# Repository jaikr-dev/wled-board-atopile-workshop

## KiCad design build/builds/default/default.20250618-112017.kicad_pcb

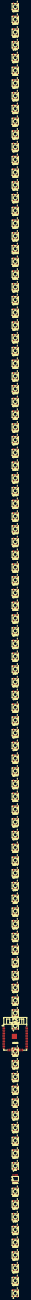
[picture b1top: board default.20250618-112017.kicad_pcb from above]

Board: 2 copper layers, 102 parts (0 on the bottom side), 3 nets, no tracks yet.

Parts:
LED1, LED2, LED3, LED4, LED5, LED6, LED7, LED8, LED9, LED10, LED11, LED12, LED13, LED14, LED15, LED16, LED17, LED18, LED19, LED20, LED21, LED22, LED23, LED24, LED25, LED26, LED27, LED28, LED29, LED30, LED31, LED32, LED33, LED34, LED35, LED36, LED37, LED38, LED39, LED40, LED41, LED42, LED43, LED44, LED45, LED46, LED47, LED48, LED49, LED50, LED51, LED52, LED53, LED54, LED55, LED56, LED57, LED58, LED59, LED60, LED61, LED62, LED63, LED64, LED65, LED66, LED67, LED68, LED69, LED70, LED71, LED72, LED73, LED74, LED75, LED76, LED77, LED78, LED79, LED80, LED81, LED82, LED83, LED84, LED85, LED86, LED87, LED88, LED89, LED90, LED91, LED92, LED93, LED94, LED95, LED96, LED97, LED98, LED99, LED100: LED-SMD_4P-L5.0-W5.0-BL_XL-5050RGBC
U1: WIFIM-SMD_ESP32-WROOM-32-N4
U2: TSSOP-14_L5.0-W4.4-P0.65-LS6.4-BL

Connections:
VDD: LED1.1, LED2.1, LED3.1, LED4.1, LED5.1, LED6.1, LED7.1, LED8.1, LED9.1, LED10.1, LED11.1, LED12.1, LED13.1, LED14.1, LED15.1, LED16.1, LED17.1, LED18.1, LED19.1, LED20.1, LED21.1, LED22.1, LED23.1, LED24.1, LED25.1, LED26.1, LED27.1, LED28.1, LED29.1, LED30.1, LED31.1, LED32.1, LED33.1, LED34.1, LED35.1, LED36.1, LED37.1, LED38.1, LED39.1, LED40.1, LED41.1, LED42.1, LED43.1, LED44.1, LED45.1, LED46.1, LED47.1, LED48.1, LED49.1, LED50.1, LED51.1, LED52.1, LED53.1, LED54.1, LED55.1, LED56.1, LED57.1, LED58.1, LED59.1, LED60.1, LED61.1, LED62.1, LED63.1, LED64.1, LED65.1, LED66.1, LED67.1, LED68.1, LED69.1, LED70.1, LED71.1, LED72.1, LED73.1, LED74.1, LED75.1, LED76.1, LED77.1, LED78.1, LED79.1, LED80.1, LED81.1, LED82.1, LED83.1, LED84.1, LED85.1, LED86.1, LED87.1, LED88.1, LED89.1, LED90.1, LED91.1, LED92.1, LED93.1, LED94.1, LED95.1, LED96.1, LED97.1, LED98.1, LED99.1, LED100.1
esp32Controller-GND: U1.1, U1.15, U1.38, U1.39
gnd: LED1.3, LED2.3, LED3.3, LED4.3, LED5.3, LED6.3, LED7.3, LED8.3, LED9.3, LED10.3, LED11.3, LED12.3, LED13.3, LED14.3, LED15.3, LED16.3, LED17.3, LED18.3, LED19.3, LED20.3, LED21.3, LED22.3, LED23.3, LED24.3, LED25.3, LED26.3, LED27.3, LED28.3, LED29.3, LED30.3, LED31.3, LED32.3, LED33.3, LED34.3, LED35.3, LED36.3, LED37.3, LED38.3, LED39.3, LED40.3, LED41.3, LED42.3, LED43.3, LED44.3, LED45.3, LED46.3, LED47.3, LED48.3, LED49.3, LED50.3, LED51.3, LED52.3, LED53.3, LED54.3, LED55.3, LED56.3, LED57.3, LED58.3, LED59.3, LED60.3, LED61.3, LED62.3, LED63.3, LED64.3, LED65.3, LED66.3, LED67.3, LED68.3, LED69.3, LED70.3, LED71.3, LED72.3, LED73.3, LED74.3, LED75.3, LED76.3, LED77.3, LED78.3, LED79.3, LED80.3, LED81.3, LED82.3, LED83.3, LED84.3, LED85.3, LED86.3, LED87.3, LED88.3, LED89.3, LED90.3, LED91.3, LED92.3, LED93.3, LED94.3, LED95.3, LED96.3, LED97.3, LED98.3, LED99.3, LED100.3

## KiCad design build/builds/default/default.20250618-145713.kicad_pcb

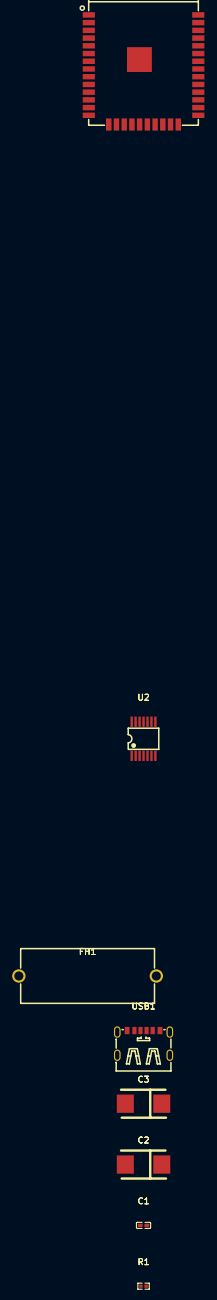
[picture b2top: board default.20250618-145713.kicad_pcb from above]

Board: 2 copper layers, 8 parts (0 on the bottom side), 6 nets, no tracks yet.

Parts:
C1: 100nF ±10% 16V X7R; C0402
C2, C3: 470µF ±10%; CASE-D_7343
FH1: FUSE-TH_L22.0-W9.0-P22.60
R1: 100Ω ±1% 62.5mW; R0402
U1: WIFIM-SMD_ESP32-WROOM-32-N4
U2: TSSOP-14_L5.0-W4.4-P0.65-LS6.4-BL
USB1: TYPE-C-SMD_TYPE-C-6P

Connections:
P1A: U1.26, U2.2
P1Y: R1.1, U2.3
P3V3: C2.2, U1.2
VCC: C1.2, FH1.2, U2.14
VDD: C3.2, FH1.1, USB1.A9, USB1.B9
gnd: C1.1, C2.1, C3.1, U1.1, U1.15, U1.38, U1.39, U2.1, U2.4, U2.5, U2.7, U2.9, U2.10, U2.12, U2.13, USB1.A12, USB1.B12
